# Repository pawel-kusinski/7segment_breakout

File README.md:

# 7-Segment Breakout Board

This is a KiCad project for a 7-segment display breakout board.

## Description

The 7-segment breakout board includes a 7-segment display and a 74LS47 Decoder/Driver. This board is a handy tool for building prototypes on a breadboard with these components. There's no need to wire all those connections and resistors manually, reducing the mess on the breadboard.

## PDF Schematic

The project is created in KiCad. If you need to check the schematic without using KiCad, the exported schematic can be found in the `schematic_pdf` directory.

## Test Code

A simple Arduino project for verifying that the board works properly can be found in the `tester` directory.

## Gerber Files

The files that can be sent to a PCB manufacturer can be found in the `fabrication_outputs` directory.

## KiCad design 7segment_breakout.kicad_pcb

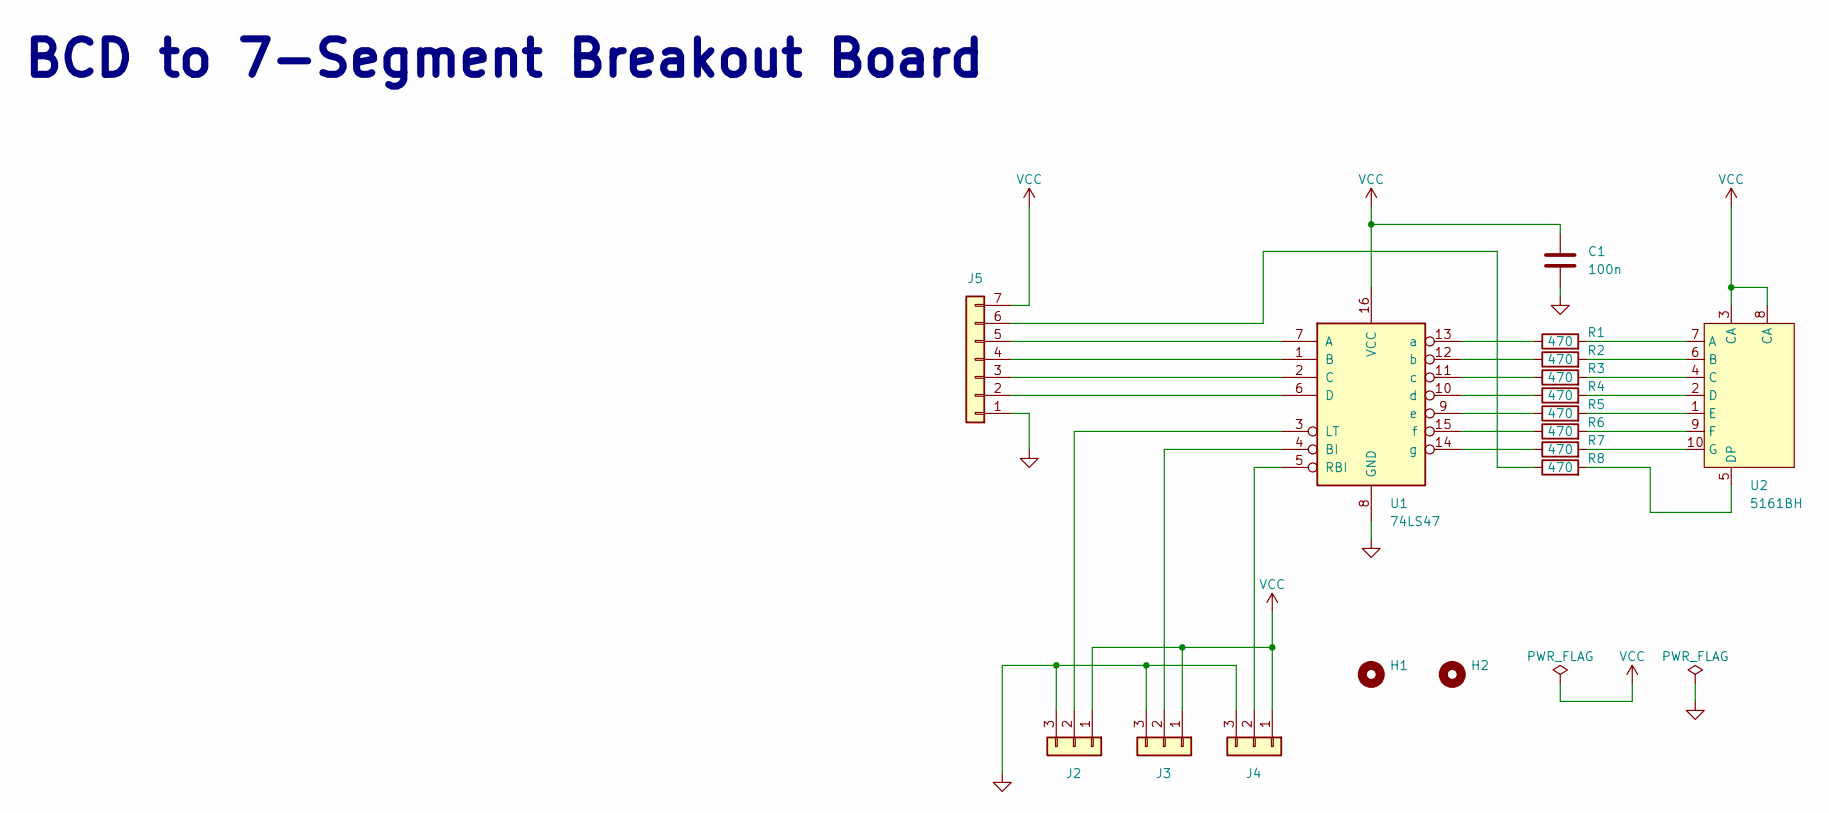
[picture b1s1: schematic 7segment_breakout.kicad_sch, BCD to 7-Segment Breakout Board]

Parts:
C1: 100n; C_0805_2012Metric_Pad1.18x1.45mm_HandSolder
H1, H2: MountingHole; MountingHole_2.2mm_M2
J2, J3, J4: Conn_01x03; PinHeader_1x03_P2.54mm_Vertical
J5: Conn_01x07; PinHeader_1x07_P2.54mm_Vertical
R1, R2, R3, R4, R5, R6, R7, R8: 470; R_0805_2012Metric_Pad1.20x1.40mm_HandSolder
U1: 74LS47; DIP-16_W7.62mm
U2: 5161BH; 5161BH_CA_LED_7-Segment_Display

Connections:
GND: C1.2, J2.3, J3.3, J4.3, J5.1, U1.8 (GND)
unnamed: J2.2, U1.3 (LT)
unnamed: J3.2, U1.4 (BI)
unnamed: J4.2, U1.5 (RBI)
unnamed: J5.2, U1.6 (D)
unnamed: J5.3, U1.2 (C)
unnamed: J5.4, U1.1 (B)
unnamed: J5.5, U1.7 (A)
unnamed: J5.6, R8.1
unnamed: R1.1, U1.13 (a)
unnamed: R2.1, U1.12 (b)
unnamed: R3.1, U1.11 (c)
unnamed: R4.1, U1.10 (d)
unnamed: R5.1, U1.9 (e)
unnamed: R6.1, U1.15 (f)
unnamed: R7.1, U1.14 (g)
unnamed: R1.2, U2.7 (A)
unnamed: R2.2, U2.6 (B)
unnamed: R3.2, U2.4 (C)
unnamed: R4.2, U2.2 (D)
unnamed: R8.2, U2.5 (DP)
unnamed: R5.2, U2.1 (E)
unnamed: R6.2, U2.9 (F)
unnamed: R7.2, U2.10 (G)
VCC: C1.1, J2.1, J3.1, J4.1, J5.7, U1.16 (VCC), U2.3 (CA), U2.8 (CA)

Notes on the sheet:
BCD to 7-Segment Breakout Board

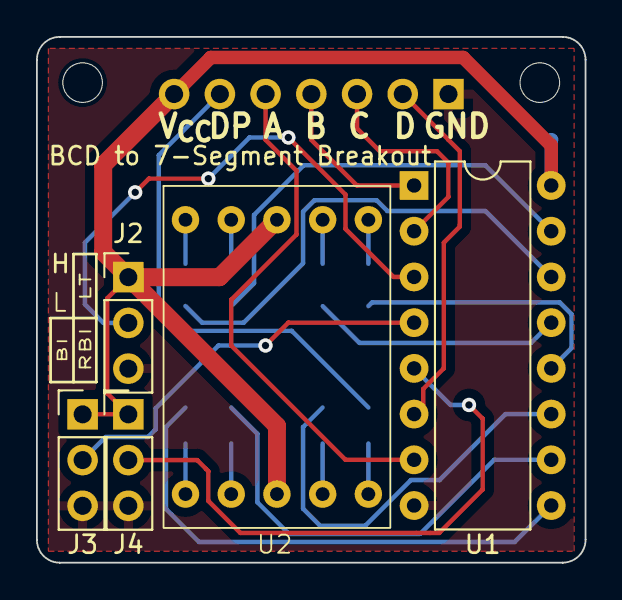
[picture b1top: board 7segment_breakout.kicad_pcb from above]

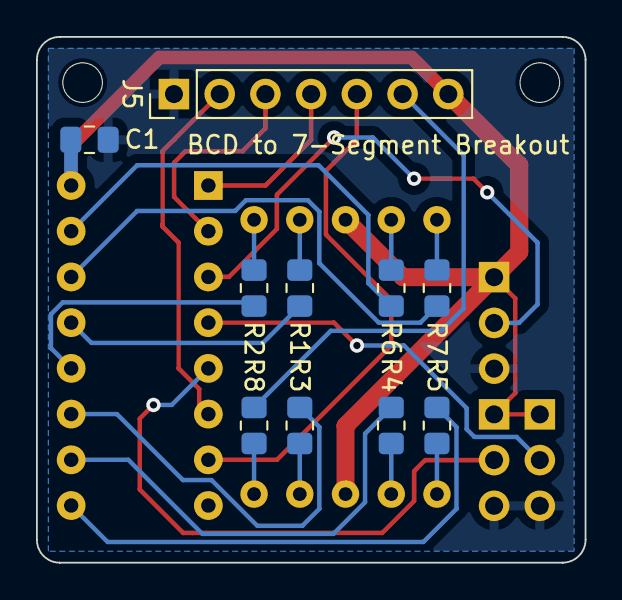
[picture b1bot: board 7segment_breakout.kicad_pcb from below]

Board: 2 copper layers, 30.5 x 29.2 mm, 17 parts (10 on the bottom side), 25 nets.
